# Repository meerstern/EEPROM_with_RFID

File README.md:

# EEPROM_with_RFID
Grove extension board of M24SR64.

[デュアルインタフェースEEPROM M24SR64][1]とアンテナを搭載したI2C Groveモジュールです。  
EEPROMにI2CとRFIDの2つの通信で内部のデータにアクセスできます。  
RFIDの通信の場合はEEPROMに電源を供給せずともRFIDの電波でそのままパッシブにEEPROMが動作します。  

一般的なEEPROMと異なり、NDEF(NFC Data Exchange Format)方式でEEPROMにデータを書き込む必要があります。  
一般的なEEPROMの様にバイト、ページ単位での書き込みには対応していません。  
NDEF(NFC Data Exchange Format)方式で書き込むためには数10kバイト以上のRAMメモリ領域が必要です。  
そのため、ArduinoUNO、PIC、F3以下のSTM32マイコン等での動作保証はできません。  
URLを書き込むSTM32F401のサンプルコードを用意しています。  

[EEPROM M24SR64][1]はISO 14443 NFC/RFID tag NFC forum Type 4 に対応しています。
  
なお、NFCリーダ/ライタはNFCタグやNFCカードを駆動させる電波を発するため技適が必要ですが、  
本モジュールはパッシブ(NFCタグやNFCカード側)のため、技適は不要です。  

[1]: https://www.st.com/ja/nfc/m24sr64-y.html "*1"

License - MIT

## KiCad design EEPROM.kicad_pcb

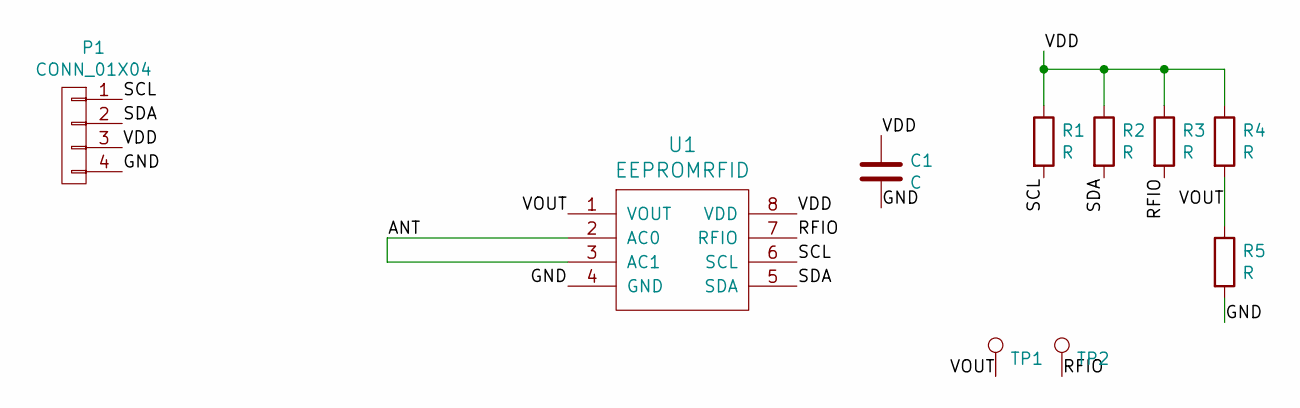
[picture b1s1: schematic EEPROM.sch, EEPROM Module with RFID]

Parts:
C1: C; generic-SMD1608
P1: CONN_01X04; GROVE
R1, R2, R3, R4, R5: R; generic-SMD1608
TP1, TP2: TEST_1P; pinhead-1X01
U1: EEPROMRFID; 8

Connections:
/ANT: U1.2 (AC0), U1.3 (AC1)
/GND: C1.2, P1.4, R5.2, U1.4 (GND)
/RFIO: R3.2, TP2.1, U1.7 (RFIO)
/SCL: P1.1, R1.2, U1.6 (SCL)
/SDA: P1.2, R2.2, U1.5 (SDA)
/VDD: C1.1, P1.3, R1.1, R2.1, R3.1, R4.1, U1.8 (VDD)
/VOUT: R4.2, R5.1, TP1.1, U1.1 (VOUT)

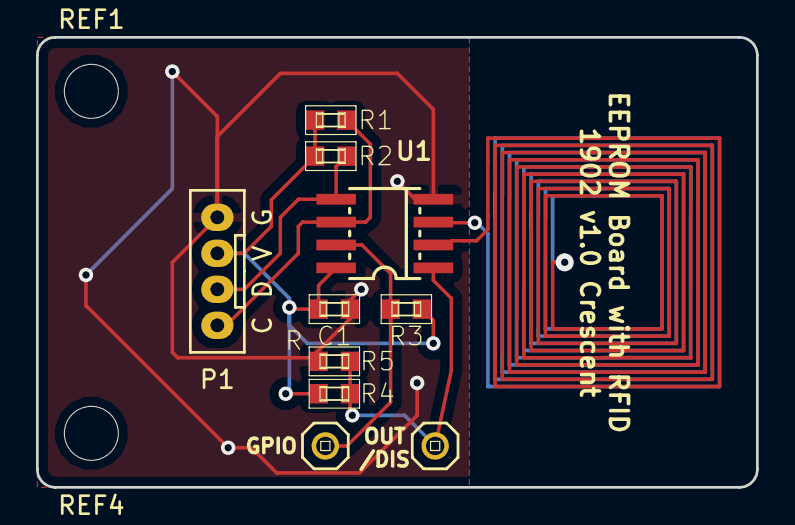
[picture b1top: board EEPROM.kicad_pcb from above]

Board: 2 copper layers, 40.0 x 25.0 mm, 12 parts (0 on the bottom side), 7 nets.

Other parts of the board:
REF1, REF4: MountingHole_3mm

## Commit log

2019-04-05 Init
2019-04-06 Add photos
